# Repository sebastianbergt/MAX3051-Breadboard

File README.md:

# MAX3051-Breadboard
Tiny Breadboard compatible pcb for experimenting with CAN.

Tiny 3.3V CAN Tranceiver with adjustable Slew Rate via potentiometer.
According to the [datasheet](https://datasheets.maximintegrated.com/en/ds/MAX3051.pdf) a resistance of 24kOhm allows a connection speed of 500 Kbit with unshielded twisted pair wires.

### Build status

Not confirmed working yet.

06/21/2019 - PCB designed

### License

    /*
     * ----------------------------------------------------------------------------
     * "THE BEER-WARE LICENSE SB":
     * Sebastian Bergt created this schematic and board file. As long as you retain this notice you
     * can do whatever you want with this stuff. If we meet some day, and you think
     * this stuff is worth it, you can buy me a beer in return.
     * ----------------------------------------------------------------------------
     */
     
Similar source: https://fedoraproject.org/wiki/Licensing/Beerware

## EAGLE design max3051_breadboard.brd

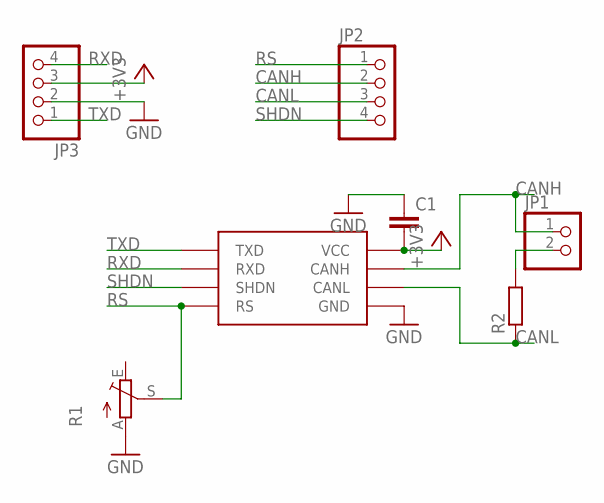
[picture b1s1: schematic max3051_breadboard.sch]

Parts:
C1: C-EUC0603; C0603
JP1: PINHD-1X2; 1X02
JP2, JP3: PINHD-1X4; 1X04
R1: TRIM_EU-S64W; S64W
R2: R-EU_R0603; R0603
SOT1: MAX3051ESA; SO-08

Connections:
+3V3: C1.2, JP3.3, SOT1.3 (VCC)
CANH: JP1.1, JP2.2, SOT1.7 (CANH)
CANL: JP2.3, R2.1, SOT1.6 (CANL)
GND: C1.1, JP3.2, R1.A, SOT1.2 (GND)
unnamed: JP1.2, R2.2
RS: JP2.1, R1.S, SOT1.8 (RS)
RXD: JP3.4, SOT1.4 (RXD)
SHDN: JP2.4, SOT1.5 (SHDN)
TXD: JP3.1, SOT1.1 (TXD)

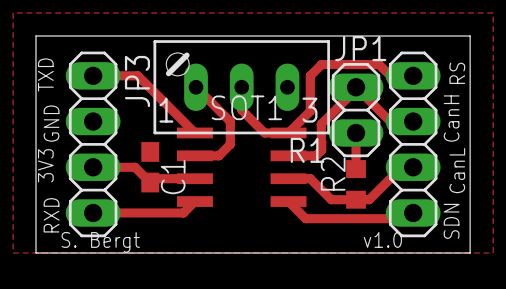
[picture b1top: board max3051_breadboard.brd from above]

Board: 2 copper layers, 24.1 x 12.1 mm, 7 parts (0 on the bottom side), 9 nets.

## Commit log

2019-07-20 version 1.0
